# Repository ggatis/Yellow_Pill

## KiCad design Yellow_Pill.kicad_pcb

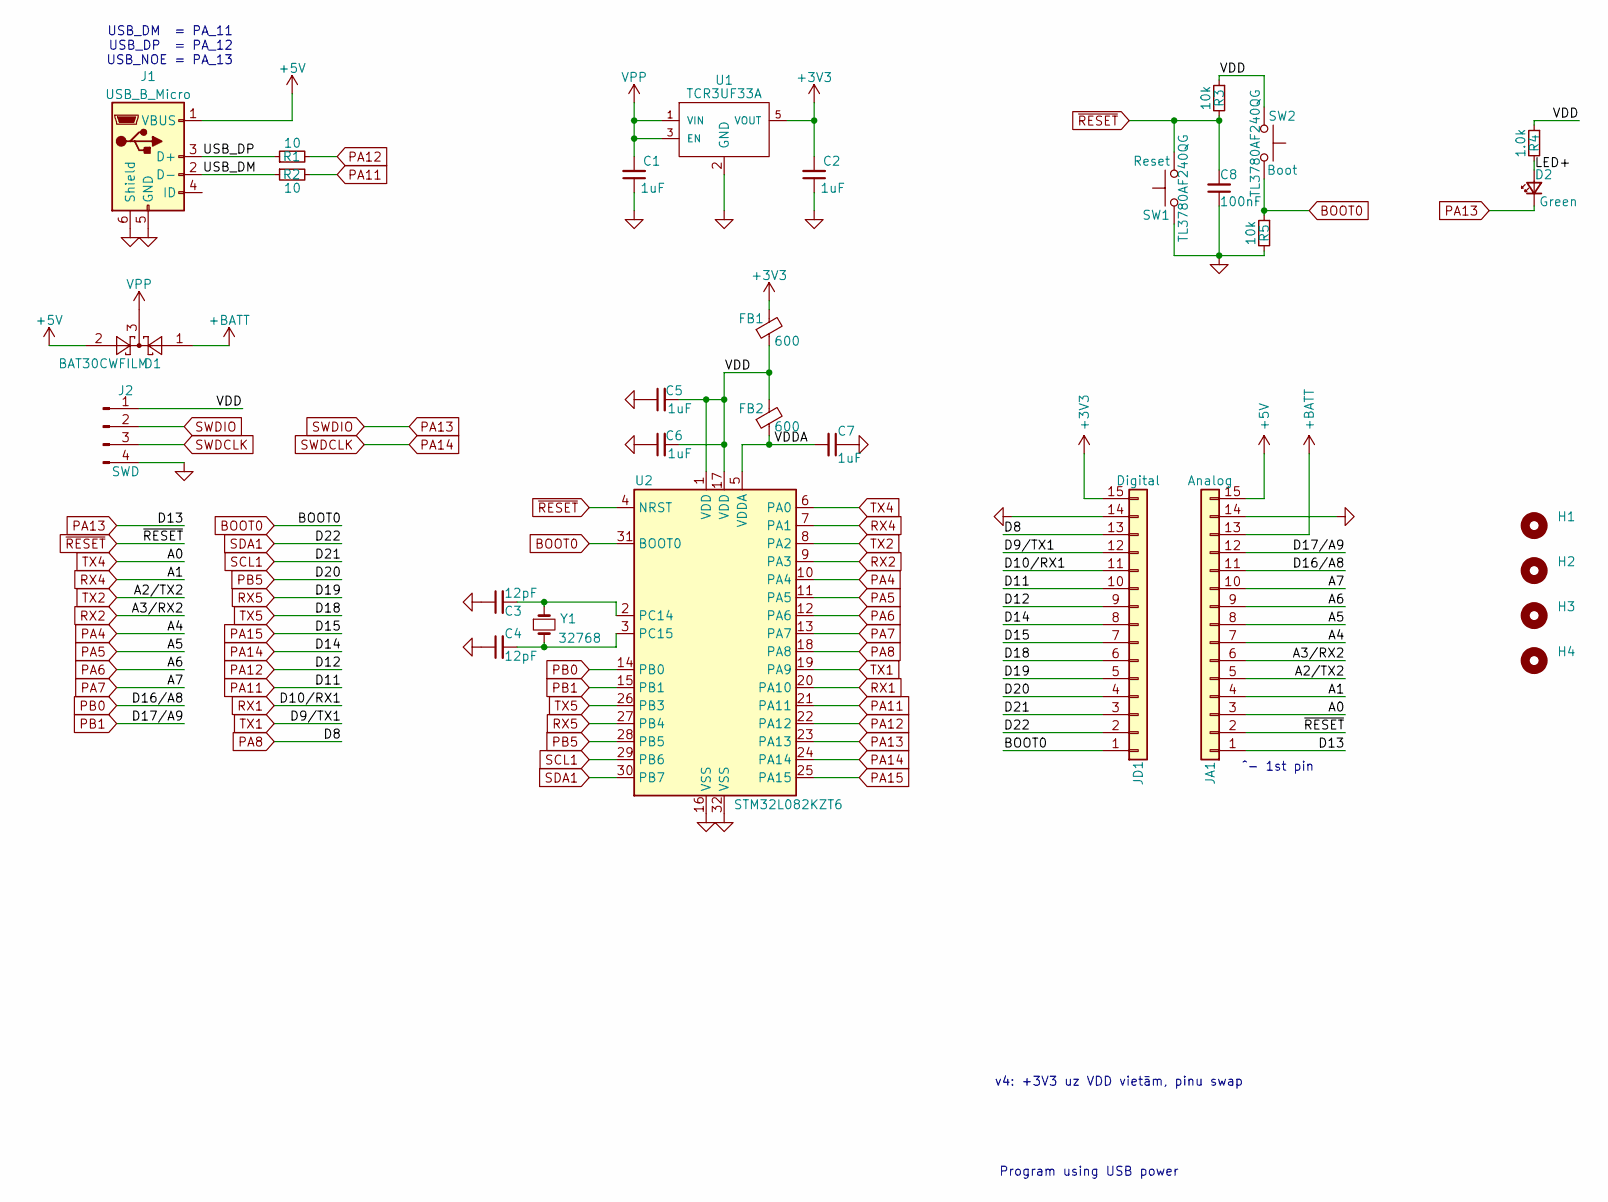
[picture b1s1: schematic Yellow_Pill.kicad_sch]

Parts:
C1, C2, C5, C6, C7: 1uF; C_0402_1005Metric; MPN CL05X105KQ5NNNC
C3, C4: 12pF; C_0402_1005Metric; MPN C0402C120J5GAC7867
C8: 100nF; C_0402_1005Metric; MPN KGM05AR71C104KH
D1: BAT30CWFILM; SOT-323_SC-70; MPN BAT30CWFILM
D2: Green; LED_0402_1005Metric_addd01mm; MPN 150040VS73240
FB1, FB2: 600; Ferrite_0603_1608Metric; MPN MH1608-601Y
H1, H2, H3, H4: MountingHole_2.7mm_M2.5_DIN965_Pad; MountingHole_1.7mm
J1: USB_B_Micro; USB_Micro-B_Wuerth_629105150521_CircularHoles_plus; MPN 629105150521
J2: SWD; PinHeader_1x04_P2.54mm_Horizontal; MPN 9-103765-0-04
JA1: Analog; PinHeader_1x15_P2.54mm_Vertical; MPN 4-103747-0-15
JD1: Digital; PinHeader_1x15_P2.54mm_Vertical; MPN 4-103747-0-15
R1, R2: 10; R_0402_1005Metric; MPN PFR05S-100-FNH
R3, R5: 10k; R_0402_1005Metric; MPN RC0402FR-0710KL
R4: 1.0k; R_0402_1005Metric; MPN RC0402FR-071KL
SW1, SW2: TL3780AF240QG; SW_TL3780AF240QG_added01mm; MPN TL3780AF240QG
U1: TCR3UF33A; SOT-25; MPN TCR3UF33A
U2: STM32L082KZT6; LQFP-32_7x7mm_P0.8mm; MPN STM32L082KZT6
Y1: 32768; Crystal_SMD_3215-2Pin_3.2x1.5mm_plus; MPN FC-135 32768Hz 12.5 +-20

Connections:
+3V3: C2.2, FB1.2, JD1.15, U1.5 (VOUT)
+5V: D1.2, J1.1 (VBUS), JA1.15
+BATT: D1.1, JA1.13
/LED+: D2.2 (A), R4.2
/USB_DM: J1.2 (D-), R2.1
/USB_DP: J1.3 (D+), R1.1
/VDD: C5.2, C6.2, FB1.1, FB2.2, J2.1, R3.1, R4.1, SW2.2, U2.1 (VDD), U2.17 (VDD)
/VDDA: C7.2, FB2.1, U2.5 (VDDA)
BOOT0: JD1.1, R5.1, SW2.1, U2.31 (BOOT0)
GND: C1.1, C2.1, C3.1, C4.1, C5.1, C6.1, C7.1, C8.1, J1.5 (GND), J1.6 (Shield), J2.4, JA1.14, JD1.14, R5.2, SW1.2, U1.2 (GND), U2.16 (VSS), U2.32 (VSS)
unnamed: C3.2, U2.2 (PC14), Y1.1
unnamed: C4.2, U2.3 (PC15), Y1.2
PA4: JA1.7, U2.10 (PA4)
PA5: JA1.8, U2.11 (PA5)
PA6: JA1.9, U2.12 (PA6)
PA7: JA1.10, U2.13 (PA7)
PA8: JD1.13, U2.18 (PA8)
PA11: JD1.10, R2.2, U2.21 (PA11)
PA12: JD1.9, R1.2, U2.22 (PA12)
PA13: D2.1 (K), J2.2, JA1.1, U2.23 (PA13)
PA14: J2.3, JD1.8, U2.24 (PA14)
PA15: JD1.7, U2.25 (PA15)
PB0: JA1.11, U2.14 (PB0)
PB1: JA1.12, U2.15 (PB1)
PB5: JD1.4, U2.28 (PB5)
RX1: JD1.11, U2.20 (PA10)
RX2: JA1.6, U2.9 (PA3)
RX4: JA1.4, U2.7 (PA1)
RX5: JD1.5, U2.27 (PB4)
SCL1: JD1.3, U2.29 (PB6)
SDA1: JD1.2, U2.30 (PB7)
TX1: JD1.12, U2.19 (PA9)
TX2: JA1.5, U2.8 (PA2)
TX4: JA1.3, U2.6 (PA0)
TX5: JD1.6, U2.26 (PB3)
VPP: C1.2, D1.3, U1.1 (VIN), U1.3 (EN)
~RESET: C8.2, JA1.2, R3.2, SW1.1, U2.4 (NRST)

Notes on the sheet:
USB_DM = PA_11 USB_DP = PA_12 USB_NOE = PA_13
v4: +3V3 uz VDD vietām, pinu swap
Program using USB power
^- 1st pin

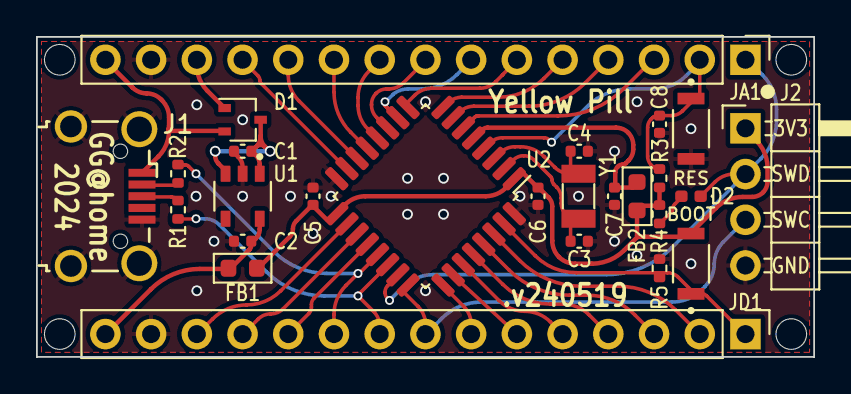
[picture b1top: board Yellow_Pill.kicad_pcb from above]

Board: 2 copper layers, 43.2 x 17.8 mm, 30 parts (0 on the bottom side), 37 nets.

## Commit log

2024-06-03 initial commit 2
